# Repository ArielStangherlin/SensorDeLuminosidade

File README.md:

# SensorDeLuminosidade
O projeto envolve a prototipagem e criação de uma PCI no KiCad de um sensor de luminosidade utilizando um LDR, LED, Resistores de 10,1k.

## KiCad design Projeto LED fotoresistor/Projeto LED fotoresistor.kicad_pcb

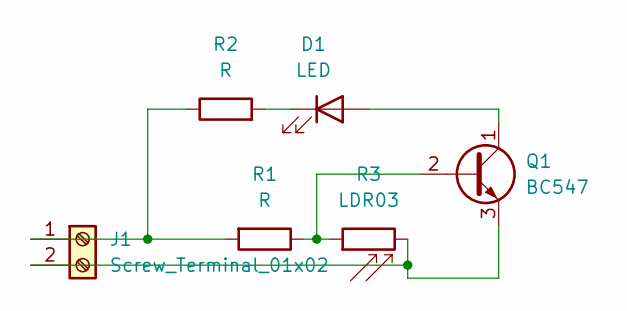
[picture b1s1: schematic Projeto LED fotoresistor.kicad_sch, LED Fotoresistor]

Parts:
D1: LED; LED_D5.0mm
J1: Screw_Terminal_01x02; TerminalBlock_MaiXu_MX126-5.0-02P_1x02_P5.00mm
Q1: BC547; TO-92L_Inline_Wide
R1, R2: R; R_Axial_DIN0204_L3.6mm_D1.6mm_P7.62mm_Horizontal
R3: LDR03; R_LDR_5.0x4.1mm_P3mm_Vertical

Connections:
unnamed: D1.2 (A), Q1.1 (C)
unnamed: D1.1 (K), R2.2
unnamed: J1.1, R1.2, R2.1
unnamed: J1.2, Q1.3 (E), R3.2
unnamed: Q1.2 (B), R1.1, R3.1

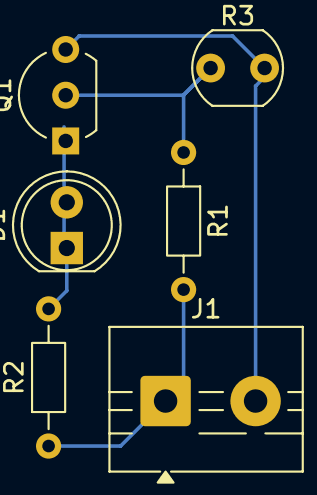
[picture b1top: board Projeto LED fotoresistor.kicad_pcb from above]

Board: 2 copper layers, 6 parts (0 on the bottom side), 5 nets.
